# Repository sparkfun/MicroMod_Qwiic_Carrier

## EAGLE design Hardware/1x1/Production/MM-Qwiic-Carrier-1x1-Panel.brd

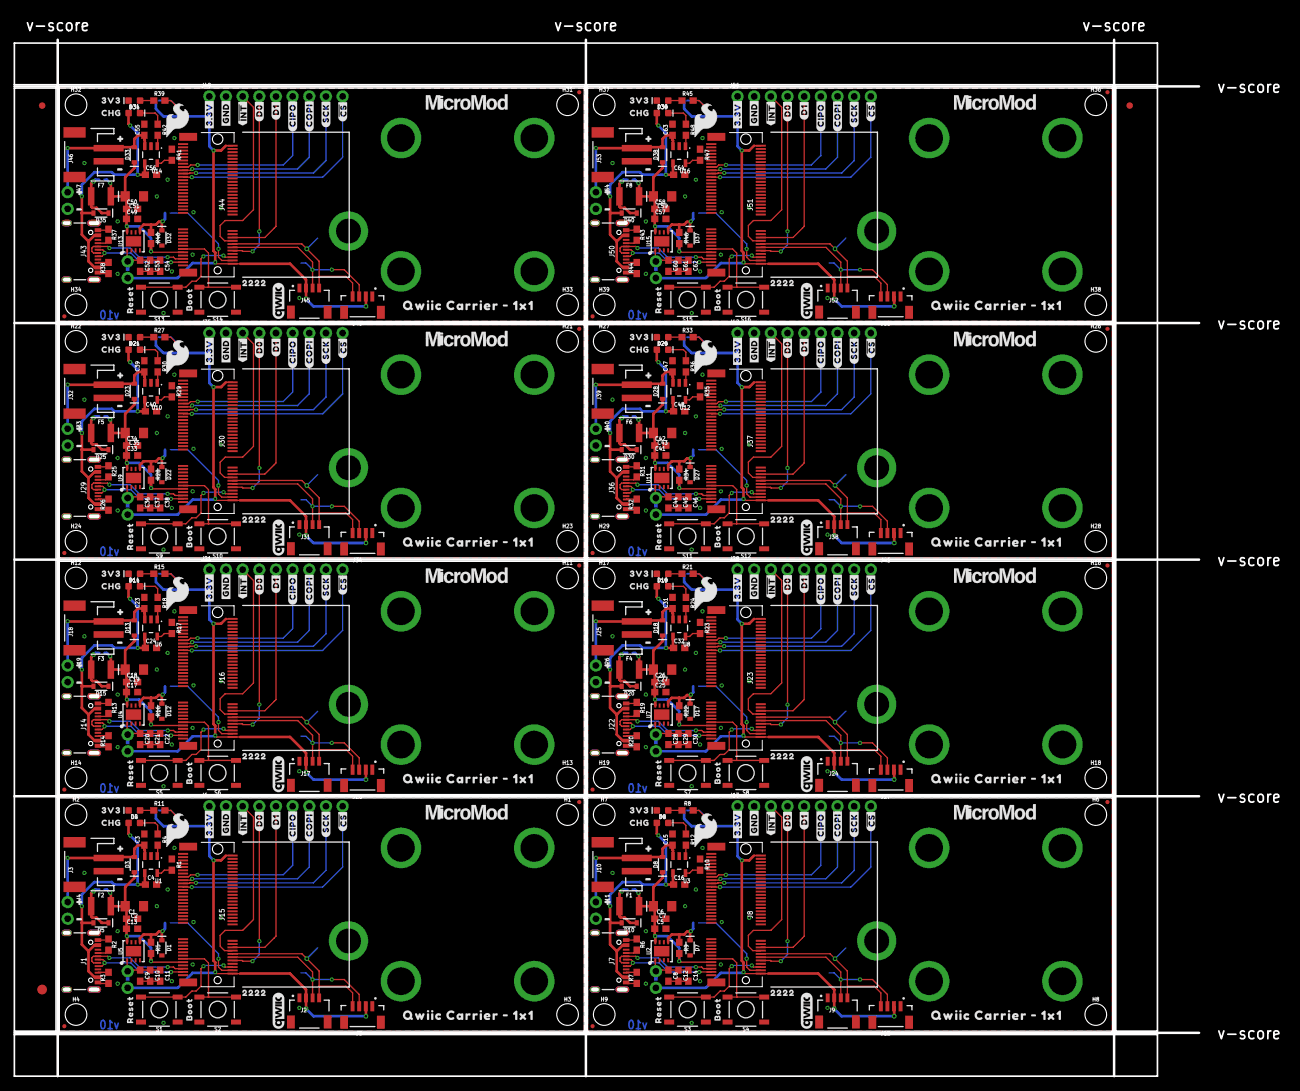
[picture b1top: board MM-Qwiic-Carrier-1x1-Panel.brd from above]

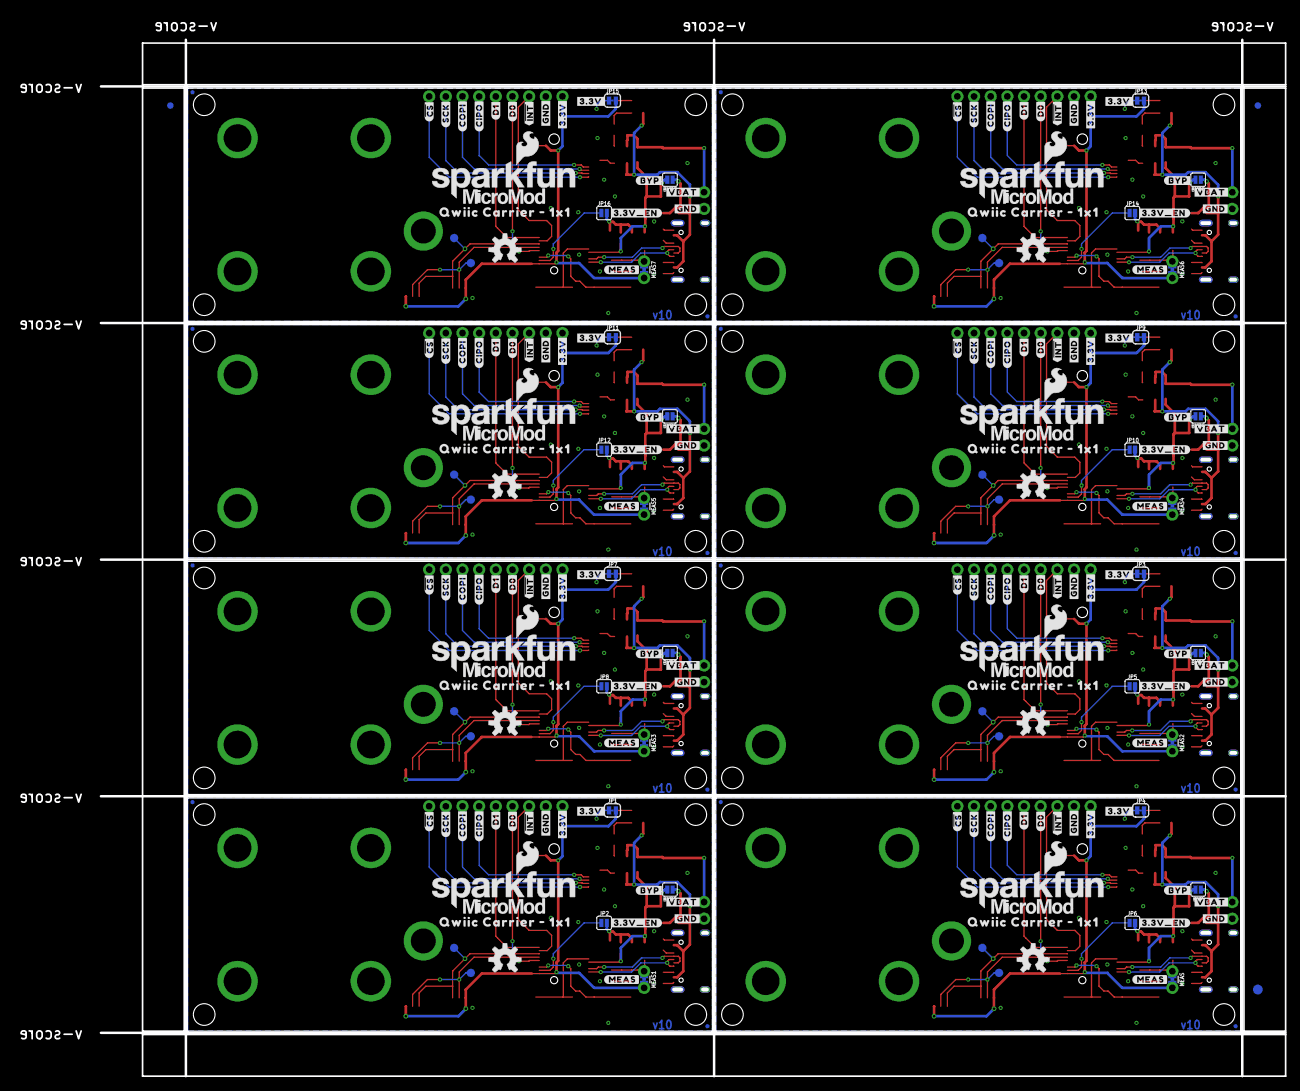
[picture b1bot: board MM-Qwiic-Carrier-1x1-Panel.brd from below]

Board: 2 copper layers, 180.6 x 158.0 mm, 710 parts (219 on the bottom side), 232 nets.

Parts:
BYP, BYP1, BYP2, BYP3, BYP4, BYP5, BYP6, BYP7: JUMPER-SMT_2_NO_SILK; SMT-JUMPER_2_NO_SILK
C1, C6, C18, C26, C34, C42, C50, C58: 0.1uF; 0603
C2, C7, C19, C27, C35, C43, C51, C59: 10uF; EIA3216
C3, C4, C15, C16, C23, C24, C31, C32, C39, C40, C47, C48, C55, C56, C63, C64: 4.7uF; 0603
C5, C11, C13, C14, C17, C22, C25, C30, C33, C38, C41, C46, C49, C54, C57, C62: 0.22uF; 0603
C8, C9, C20, C28, C36, C44, C52, C60: 10uF; 0603
C10, C12, C21, C29, C37, C45, C53, C61: 1.0uF; 0603
D1, D7, D12, D17, D22, D27, D32, D37: 3.3V; SOD-323
D2, D6, D11, D16, D21, D26, D31, D36: RED; LED-0603
D3, D5, D8, D10, D13, D15, D18, D20, D23, D25, D28, D30, D33, D35, D38, D40: 3A/10V/280mV; SOD-323
D4, D9, D14, D19, D24, D29, D34, D39: Yellow; LED-0603
E$1, E$2, E$3, E$4: FIDUCIAL-1X2
E$5, E$6: FIDUCIAL-1.5X3
F1, F2, F3, F4, F5, F6, F7, F8: 6V/2A; 1210
FD1, FD2, FD3, FD4, FD5, FD6, FD7, FD8, FD9, FD10, FD11, FD12, FD13, FD14, FD15, FD16, FD17, FD18, FD19, FD20, FD21, FD22, FD23, FD24, FD25, FD26, FD27, FD28, FD29, FD30, FD31, FD32: FIDUCIALUFIDUCIAL; FIDUCIAL-MICRO
H1, H2, H3, H4, H6, H7, H8, H9, H11, H12, H13, H14, H16, H17, H18, H19, H21, H22, H23, H24, H26, H27, H28, H29, H31, H32, H33, H34, H36, H37, H38, H39: STAND-OFF
H5, H10, H15, H20, H25, H30, H35, H40: STAND-OFF-REFLOW2.5MM_TALL; STAND-OFF-REFLOW-M2.5
J1, J7, J14, J22, J29, J36, J43, J50: USB-C-16P-2LAYER-PADS
J2, J9, J17, J24, J31, J38, J45, J52: QWIIC_RIGHT_ANGLE; JST04_1MM_RA
J3, J10, J18, J25, J32, J39, J46, J53: JST-2-SMD
J4, J11, J19, J26, J33, J40, J47, J54: 1X02_NO_SILK
J5, J12, J20, J27, J34, J41, J48, J55: Vertical Qwiic Connector; JST04_1MM_VERT
J6, J13, J21, J28, J35, J42, J49, J56: 1X09_NO_SILK
J8, J15, J16, J23, J30, J37, J44, J51: MICROMOD-2222-C; M.2-CONNECTOR-E
JP1, JP3, JP4, JP7, JP9, JP11, JP13, JP15: 3V3 LED; SMT-JUMPER_2_NC_TRACE_SILK
JP2, JP5, JP6, JP8, JP10, JP12, JP14, JP16: VE; SMT-JUMPER_2_NO_SILK
LOGO1, LOGO6, LOGO9, LOGO12, LOGO15, LOGO18, LOGO21, LOGO24: SFE_LOGO_NAME_FLAME.2_INCH; SFE_LOGO_NAME_FLAME_.2
LOGO2, LOGO4, LOGO7, LOGO10, LOGO13, LOGO16, LOGO19, LOGO22: QWIIC_LOGO_CONNECTOR; QWIIC_5.5MM
LOGO3, LOGO5, LOGO8, LOGO11, LOGO14, LOGO17, LOGO20, LOGO23: OSHW-LOGOM; OSHW-LOGO-M
MEAS, MEAS1, MEAS2, MEAS3, MEAS4, MEAS5, MEAS6, MEAS7: COMBO-JUMPER_2_NC_TRACE
R1, R10, R17, R23, R29, R35, R41, R47: 2.2k; 0603
R2, R3, R6, R7, R13, R14, R19, R20, R25, R26, R31, R32, R37, R38, R43, R44: 5.1k; 0603
R4, R8, R11, R12, R15, R18, R21, R24, R27, R30, R33, R36, R39, R42, R45, R48: 1k; 0603
R5, R9, R16, R22, R28, R34, R40, R46: 100k; 0603
S1, S3, S5, S7, S9, S11, S13, S15: Reset; TACTILE_SWITCH_SMD_5.2MM
S2, S4, S6, S8, S10, S12, S14, S16: BOOT; TACTILE_SWITCH_SMD_5.2MM
TP1, TP2, TP3, TP4, TP5, TP6, TP7, TP8, TP9, TP10, TP11, TP12, TP13, TP14, TP15, TP16: TEST-POINT3X5; PAD.03X.05
U1, U3, U6, U8, U10, U12, U14, U16: MCP73831; SOT23-5
U2, U4, U5, U7, U9, U11, U13, U15: AP7361C-33FGEUDFN-8; UDFN-8
U$1, U$49, U$90, U$129, U$168, U$207, U$246, U$285: #3#3V_EN#0
U$2, U$44, U$79, U$118, U$157, U$196, U$235, U$274: SFE_LOGO_FLAME_.2
U$3, U$48, U$89, U$128, U$167, U$206, U$245, U$284: 3V30
U$4, U$40, U$82, U$121, U$160, U$199, U$238, U$277: CHG0
U$5, U$45, U$86, U$125, U$164, U$203, U$242, U$281: QWIIC_BOARD_OUTLINESTANDOFF; QWIIC_BOARD_MOUNT_SMD_STANDOFFS
U$6, U$35, U$38, U$41, U$73, U$74, U$83, U$112, U$113, U$122, U$151, U$152, U$161, U$190, U$191, U$200, U$229, U$230, U$239, U$268, U$269, U$278, U$307, U$308: #3#3V#0
U$7, U$42, U$84, U$123, U$162, U$201, U$240, U$279: #BYP#0
U$8, U$14, U$33, U$50, U$51, U$59, U$91, U$92, U$100, U$130, U$131, U$139, U$169, U$170, U$178, U$208, U$209, U$217, U$247, U$248, U$256, U$286, U$287, U$295: #GND#0
U$9, U$43, U$85, U$124, U$163, U$202, U$241, U$280: #MEAS#0
U$10, U$13, U$46, U$47, U$87, U$88, U$126, U$127, U$165, U$166, U$204, U$205, U$243, U$244, U$282, U$283: QWIIC_CARRIER_#_1X10
U$11, U$32, U$36, U$37, U$60, U$61, U$62, U$63, U$101, U$102, U$103, U$104, U$140, U$141, U$142, U$143, U$179, U$180, U$181, U$182, U$218, U$219, U$220, U$221, U$257, U$258, U$259, U$260, U$296, U$297, U$298, U$299: #0
U$12, U$58, U$99, U$138, U$177, U$216, U$255, U$294: #VBAT#0
U$15, U$16, U$77, U$78, U$116, U$117, U$155, U$156, U$194, U$195, U$233, U$234, U$272, U$273, U$311, U$312: ##INT##0
U$17, U$18, U$64, U$65, U$105, U$106, U$144, U$145, U$183, U$184, U$222, U$223, U$261, U$262, U$300, U$301: #D0#0
U$19, U$39, U$67, U$68, U$80, U$81, U$119, U$120, U$158, U$159, U$197, U$198, U$236, U$237, U$275, U$276: MICROMOD_LOGO_.5
U$20, U$21, U$66, U$69, U$107, U$108, U$146, U$147, U$185, U$186, U$224, U$225, U$263, U$264, U$302, U$303: #D1#0
U$22, U$23, U$52, U$53, U$93, U$94, U$132, U$133, U$171, U$172, U$210, U$211, U$249, U$250, U$288, U$289: #CIPO#0
U$24, U$25, U$54, U$55, U$95, U$96, U$134, U$135, U$173, U$174, U$212, U$213, U$251, U$252, U$290, U$291: #COPI#0
U$26, U$27, U$56, U$57, U$97, U$98, U$136, U$137, U$175, U$176, U$214, U$215, U$253, U$254, U$292, U$293: #SCK#0
U$28, U$29, U$75, U$76, U$114, U$115, U$153, U$154, U$192, U$193, U$231, U$232, U$270, U$271, U$309, U$310: ##CS##0
U$30, U$70, U$109, U$148, U$187, U$226, U$265, U$304: RESET0
U$31, U$71, U$110, U$149, U$188, U$227, U$266, U$305: BOOT0
U$34, U$72, U$111, U$150, U$189, U$228, U$267, U$306: 22220

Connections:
3.3V: J2.2, J5.2, J6.1, J15.2, J15.74, JP4.2, MEAS.2, MEAS.4
3.3V1: J8.2, J8.74, J9.2, J12.2, J13.1, JP1.2, MEAS1.2, MEAS1.4
3.3V2: J16.2, J16.74, J17.2, J20.2, J21.1, JP3.2, MEAS2.2, MEAS2.4
3.3V3: J23.2, J23.74, J24.2, J27.2, J28.1, JP7.2, MEAS3.2, MEAS3.4
3.3V4: J30.2, J30.74, J31.2, J34.2, J35.1, JP9.2, MEAS4.2, MEAS4.4
3.3V5: J37.2, J37.74, J38.2, J41.2, J42.1, JP11.2, MEAS5.2, MEAS5.4
3.3V6: J44.2, J44.74, J45.2, J48.2, J49.1, JP13.2, MEAS6.2, MEAS6.4
3.3V7: J51.2, J51.74, J52.2, J55.2, J56.1, JP15.2, MEAS7.2, MEAS7.4
3.3V_EN: J15.4, JP6.1
3.3V_EN1: J8.4, JP2.1
3.3V_EN2: J16.4, JP5.1
3.3V_EN3: J23.4, JP8.1
3.3V_EN4: J30.4, JP10.1
3.3V_EN5: J37.4, JP12.1
3.3V_EN6: J44.4, JP14.1
3.3V_EN7: J51.4, JP16.1
!BOOT!: J15.11, S2.3, S2.4
!BOOT!1: J8.11, S4.3, S4.4
!BOOT!2: J16.11, S6.3, S6.4
!BOOT!3: J23.11, S8.3, S8.4
!BOOT!4: J30.11, S10.3, S10.4
!BOOT!5: J37.11, S12.3, S12.4
!BOOT!6: J44.11, S14.3, S14.4
!BOOT!7: J51.11, S16.3, S16.4
!RESET!: J15.6, S1.3, S1.4
!RESET!1: J8.6, S3.3, S3.4
!RESET!2: J16.6, S5.3, S5.4
!RESET!3: J23.6, S7.3, S7.4
!RESET!4: J30.6, S9.3, S9.4
!RESET!5: J37.6, S11.3, S11.4
!RESET!6: J44.6, S13.3, S13.4
!RESET!7: J51.6, S15.3, S15.4
D0: J6.4, J15.10
D1: J6.5, J15.18
D2: J8.10, J13.4
D3: J8.18, J13.5
D4: J16.10, J21.4
D5: J16.18, J21.5
D6: J23.10, J28.4
D7: J23.18, J28.5
D8: J30.10, J35.4
D9: J30.18, J35.5
D10: J37.10, J42.4
D11: J37.18, J42.5
D12: J44.10, J49.4
D13: J44.18, J49.5
D14: J51.10, J56.4
D15: J51.18, J56.5
GND: C1.2, C2.-, C3.2, C4.2, C9.2, C10.2, C11.2, C13.2, D1.A, D2.C, H5.1, J1.GND, J1.GND2, J2.1, J3.1, J4.2, J5.1, J6.2, J15.1, J15.7, J15.33, J15.36, J15.39, J15.45, J15.75, R1.1, R2.1, R3.1, S1.1, S1.2, S2.1, S2.2, U1.2, U5.4, U5.EP
GND1: C5.2, C6.2, C7.-, C8.2, C12.2, C14.2, C15.2, C16.2, D6.C, D7.A, H10.1, J7.GND, J7.GND2, J8.1, J8.7, J8.33, J8.36, J8.39, J8.45, J8.75, J9.1, J10.1, J11.2, J12.1, J13.2, R6.1, R7.1, R10.1, S3.1, S3.2, S4.1, S4.2, U2.4, U2.EP, U3.2
GND2: C17.2, C18.2, C19.-, C20.2, C21.2, C22.2, C23.2, C24.2, D11.C, D12.A, H15.1, J14.GND, J14.GND2, J16.1, J16.7, J16.33, J16.36, J16.39, J16.45, J16.75, J17.1, J18.1, J19.2, J20.1, J21.2, R13.1, R14.1, R17.1, S5.1, S5.2, S6.1, S6.2, U4.4, U4.EP, U6.2
GND3: C25.2, C26.2, C27.-, C28.2, C29.2, C30.2, C31.2, C32.2, D16.C, D17.A, H20.1, J22.GND, J22.GND2, J23.1, J23.7, J23.33, J23.36, J23.39, J23.45, J23.75, J24.1, J25.1, J26.2, J27.1, J28.2, R19.1, R20.1, R23.1, S7.1, S7.2, S8.1, S8.2, U7.4, U7.EP, U8.2
GND4: C33.2, C34.2, C35.-, C36.2, C37.2, C38.2, C39.2, C40.2, D21.C, D22.A, H25.1, J29.GND, J29.GND2, J30.1, J30.7, J30.33, J30.36, J30.39, J30.45, J30.75, J31.1, J32.1, J33.2, J34.1, J35.2, R25.1, R26.1, R29.1, S9.1, S9.2, S10.1, S10.2, U9.4, U9.EP, U10.2
GND5: C41.2, C42.2, C43.-, C44.2, C45.2, C46.2, C47.2, C48.2, D26.C, D27.A, H30.1, J36.GND, J36.GND2, J37.1, J37.7, J37.33, J37.36, J37.39, J37.45, J37.75, J38.1, J39.1, J40.2, J41.1, J42.2, R31.1, R32.1, R35.1, S11.1, S11.2, S12.1, S12.2, U11.4, U11.EP, U12.2
GND6: C49.2, C50.2, C51.-, C52.2, C53.2, C54.2, C55.2, C56.2, D31.C, D32.A, H35.1, J43.GND, J43.GND2, J44.1, J44.7, J44.33, J44.36, J44.39, J44.45, J44.75, J45.1, J46.1, J47.2, J48.1, J49.2, R37.1, R38.1, R41.1, S13.1, S13.2, S14.1, S14.2, U13.4, U13.EP, U14.2
GND7: C57.2, C58.2, C59.-, C60.2, C61.2, C62.2, C63.2, C64.2, D36.C, D37.A, H40.1, J50.GND, J50.GND2, J51.1, J51.7, J51.33, J51.36, J51.39, J51.45, J51.75, J52.1, J53.1, J54.2, J55.1, J56.2, R43.1, R44.1, R47.1, S15.1, S15.2, S16.1, S16.2, U15.4, U15.EP, U16.2
I2C_!INT!: J6.3, J15.16
I2C_!INT!1: J8.16, J13.3
I2C_!INT!2: J16.16, J21.3
I2C_!INT!3: J23.16, J28.3
I2C_!INT!4: J30.16, J35.3
I2C_!INT!5: J37.16, J42.3
I2C_!INT!6: J44.16, J49.3
I2C_!INT!7: J51.16, J56.3
unnamed: C9.1, C10.1, C11.1, MEAS.1, MEAS.3, U5.1
unnamed: R1.2, U1.5
unnamed: D4.C, R4.1
unnamed: JP4.1, R11.2
unnamed: J7.A5, R6.2
unnamed: D2.A, R11.1
unnamed: J7.B5, R7.2
unnamed: R4.2, U1.1
unnamed: JP1.1, R8.2
unnamed: J1.A5, R2.2
unnamed: J1.B5, R3.2
unnamed: D6.A, R8.1
unnamed: C8.1, C12.1, C14.1, MEAS1.1, MEAS1.3, U2.1
unnamed: R10.2, U3.5
unnamed: D9.C, R12.1
unnamed: R12.2, U3.1
unnamed: J14.A5, R13.2
unnamed: J14.B5, R14.2
unnamed: JP3.1, R15.2
unnamed: D11.A, R15.1
unnamed: C20.1, C21.1, C22.1, MEAS2.1, MEAS2.3, U4.1
unnamed: R17.2, U6.5
unnamed: D14.C, R18.1
unnamed: R18.2, U6.1
unnamed: J22.A5, R19.2
unnamed: J22.B5, R20.2
unnamed: JP7.1, R21.2
unnamed: D16.A, R21.1
unnamed: C28.1, C29.1, C30.1, MEAS3.1, MEAS3.3, U7.1
unnamed: R23.2, U8.5
unnamed: D19.C, R24.1
unnamed: R24.2, U8.1
unnamed: J29.A5, R25.2
unnamed: J29.B5, R26.2
unnamed: JP9.1, R27.2
unnamed: D21.A, R27.1
unnamed: C36.1, C37.1, C38.1, MEAS4.1, MEAS4.3, U9.1
unnamed: R29.2, U10.5
unnamed: D24.C, R30.1
unnamed: R30.2, U10.1
unnamed: J36.A5, R31.2
unnamed: J36.B5, R32.2
unnamed: JP11.1, R33.2
unnamed: D26.A, R33.1
unnamed: C44.1, C45.1, C46.1, MEAS5.1, MEAS5.3, U11.1
unnamed: R35.2, U12.5
unnamed: D29.C, R36.1
unnamed: R36.2, U12.1
unnamed: J43.A5, R37.2
unnamed: J43.B5, R38.2
unnamed: JP13.1, R39.2
unnamed: D31.A, R39.1
unnamed: C52.1, C53.1, C54.1, MEAS6.1, MEAS6.3, U13.1
unnamed: R41.2, U14.5
unnamed: D34.C, R42.1
unnamed: R42.2, U14.1
unnamed: J50.A5, R43.2
unnamed: J50.B5, R44.2
unnamed: JP15.1, R45.2
unnamed: D36.A, R45.1
unnamed: C60.1, C61.1, C62.1, MEAS7.1, MEAS7.3, U15.1
unnamed: R47.2, U16.5
unnamed: D39.C, R48.1
unnamed: R48.2, U16.1
SCL: J2.4, J5.4, J15.14, TP2.P$1
SCL1: J8.14, J9.4, J12.4, TP4.P$1
SCL2: J16.14, J17.4, J20.4, TP6.P$1
SCL3: J23.14, J24.4, J27.4, TP8.P$1
SCL4: J30.14, J31.4, J34.4, TP10.P$1
SCL5: J37.14, J38.4, J41.4, TP12.P$1
SCL6: J44.14, J45.4, J48.4, TP14.P$1
SCL7: J51.14, J52.4, J55.4, TP16.P$1
SDA: J2.3, J5.3, J15.12, TP1.P$1
SDA1: J8.12, J9.3, J12.3, TP3.P$1
SDA2: J16.12, J17.3, J20.3, TP5.P$1
SDA3: J23.12, J24.3, J27.3, TP7.P$1
SDA4: J30.12, J31.3, J34.3, TP9.P$1
SDA5: J37.12, J38.3, J41.3, TP11.P$1
SDA6: J44.12, J45.3, J48.3, TP13.P$1
SDA7: J51.12, J52.3, J55.3, TP15.P$1
SPI_!CS!: J6.9, J15.55
SPI_!CS!1: J8.55, J13.9
SPI_!CS!2: J16.55, J21.9
SPI_!CS!3: J23.55, J28.9
SPI_!CS!4: J30.55, J35.9
SPI_!CS!5: J37.55, J42.9
SPI_!CS!6: J44.55, J49.9
SPI_!CS!7: J51.55, J56.9
SPI_CIPO: J6.6, J15.61
SPI_CIPO1: J8.61, J13.6
SPI_CIPO2: J16.61, J21.6
SPI_CIPO3: J23.61, J28.6
SPI_CIPO4: J30.61, J35.6
SPI_CIPO5: J37.61, J42.6
SPI_CIPO6: J44.61, J49.6
SPI_CIPO7: J51.61, J56.6
SPI_COPI: J6.7, J15.59
SPI_COPI1: J8.59, J13.7
SPI_COPI2: J16.59, J21.7
SPI_COPI3: J23.59, J28.7
SPI_COPI4: J30.59, J35.7
SPI_COPI5: J37.59, J42.7
SPI_COPI6: J44.59, J49.7
SPI_COPI7: J51.59, J56.7
SPI_SCK: J6.8, J15.57
SPI_SCK1: J8.57, J13.8
SPI_SCK2: J16.57, J21.8
SPI_SCK3: J23.57, J28.8
SPI_SCK4: J30.57, J35.8
SPI_SCK5: J37.57, J42.8
SPI_SCK6: J44.57, J49.8
SPI_SCK7: J51.57, J56.8
USB_D+: J1.A6, J1.B6, J15.3
USB_D+1: J7.A6, J7.B6, J8.3
USB_D+2: J14.A6, J14.B6, J16.3
USB_D+3: J22.A6, J22.B6, J23.3
USB_D+4: J29.A6, J29.B6, J30.3
USB_D+5: J36.A6, J36.B6, J37.3
USB_D+6: J43.A6, J43.B6, J44.3
USB_D+7: J50.A6, J50.B6, J51.3
USB_D-: J1.A7, J1.B7, J15.5
USB_D-1: J7.A7, J7.B7, J8.5
USB_D-2: J14.A7, J14.B7, J16.5
USB_D-3: J22.A7, J22.B7, J23.5
USB_D-4: J29.A7, J29.B7, J30.5
USB_D-5: J36.A7, J36.B7, J37.5
USB_D-6: J43.A7, J43.B7, J44.5
USB_D-7: J50.A7, J50.B7, J51.5
VIN: BYP.2, C1.1, C2.+, C13.1, D3.C, F2.2, J15.9, R5.2, U5.8
VIN1: BYP1.2, C5.1, C6.1, C7.+, D8.C, F1.2, J8.9, R9.2, U2.8
VIN2: BYP2.2, C17.1, C18.1, C19.+, D13.C, F3.2, J16.9, R16.2, U4.8
VIN3: BYP3.2, C25.1, C26.1, C27.+, D18.C, F4.2, J23.9, R22.2, U7.8
VIN4: BYP4.2, C33.1, C34.1, C35.+, D23.C, F5.2, J30.9, R28.2, U9.8
VIN5: BYP5.2, C41.1, C42.1, C43.+, D28.C, F6.2, J37.9, R34.2, U11.8
VIN6: BYP6.2, C49.1, C50.1, C51.+, D33.C, F7.2, J44.9, R40.2, U13.8
VIN7: BYP7.2, C57.1, C58.1, C59.+, D38.C, F8.2, J51.9, R46.2, U15.8
VREG_EN: D1.C, JP6.2, R5.1, U5.5
VREG_EN1: D7.C, JP2.2, R9.1, U2.5
VREG_EN2: D12.C, JP5.2, R16.1, U4.5
VREG_EN3: D17.C, JP8.2, R22.1, U7.5
VREG_EN4: D22.C, JP10.2, R28.1, U9.5
VREG_EN5: D27.C, JP12.2, R34.1, U11.5
VREG_EN6: D32.C, JP14.2, R40.1, U13.5
VREG_EN7: D37.C, JP16.2, R46.1, U15.5
V_BATT: C3.1, D3.A, J3.2, J4.1, U1.3
V_BATT1: C15.1, D8.A, J10.2, J11.1, U3.3
V_BATT2: C23.1, D13.A, J18.2, J19.1, U6.3
V_BATT3: C31.1, D18.A, J25.2, J26.1, U8.3
V_BATT4: C39.1, D23.A, J32.2, J33.1, U10.3
V_BATT5: C47.1, D28.A, J39.2, J40.1, U12.3
V_BATT6: C55.1, D33.A, J46.2, J47.1, U14.3
V_BATT7: C63.1, D38.A, J53.2, J54.1, U16.3
V_USB: C4.1, D4.A, D5.A, J1.VBUS1, J1.VBUS2, U1.4
V_USB1: C16.1, D9.A, D10.A, J7.VBUS1, J7.VBUS2, U3.4
V_USB2: C24.1, D14.A, D15.A, J14.VBUS1, J14.VBUS2, U6.4
V_USB3: C32.1, D19.A, D20.A, J22.VBUS1, J22.VBUS2, U8.4
V_USB4: C40.1, D24.A, D25.A, J29.VBUS1, J29.VBUS2, U10.4
V_USB5: C48.1, D29.A, D30.A, J36.VBUS1, J36.VBUS2, U12.4
V_USB6: C56.1, D34.A, D35.A, J43.VBUS1, J43.VBUS2, U14.4
V_USB7: C64.1, D39.A, D40.A, J50.VBUS1, J50.VBUS2, U16.4
V_USB_1: BYP1.1, D10.C, F1.1
V_USB_2: BYP.1, D5.C, F2.1
V_USB_3: BYP2.1, D15.C, F3.1
V_USB_4: BYP3.1, D20.C, F4.1
V_USB_5: BYP4.1, D25.C, F5.1
V_USB_6: BYP5.1, D30.C, F6.1
V_USB_7: BYP6.1, D35.C, F7.1
V_USB_8: BYP7.1, D40.C, F8.1

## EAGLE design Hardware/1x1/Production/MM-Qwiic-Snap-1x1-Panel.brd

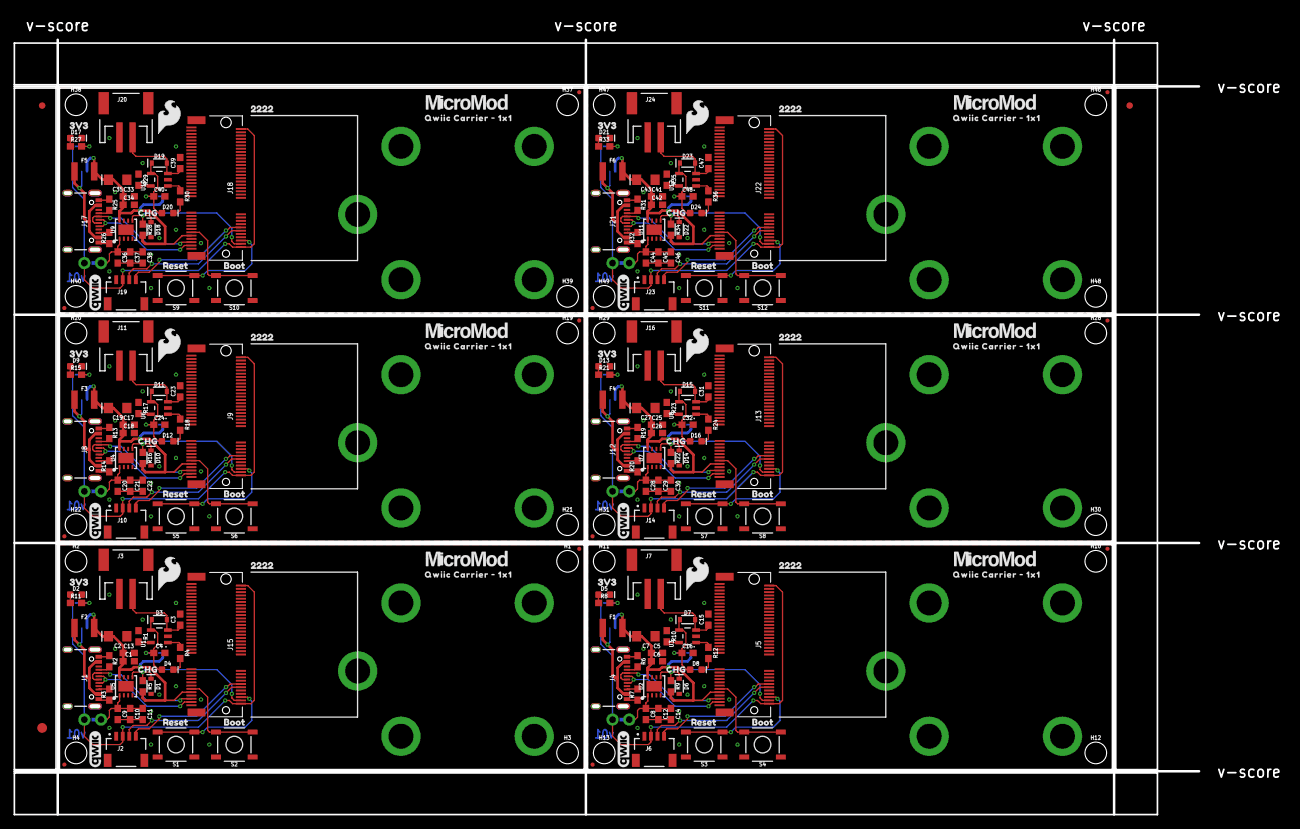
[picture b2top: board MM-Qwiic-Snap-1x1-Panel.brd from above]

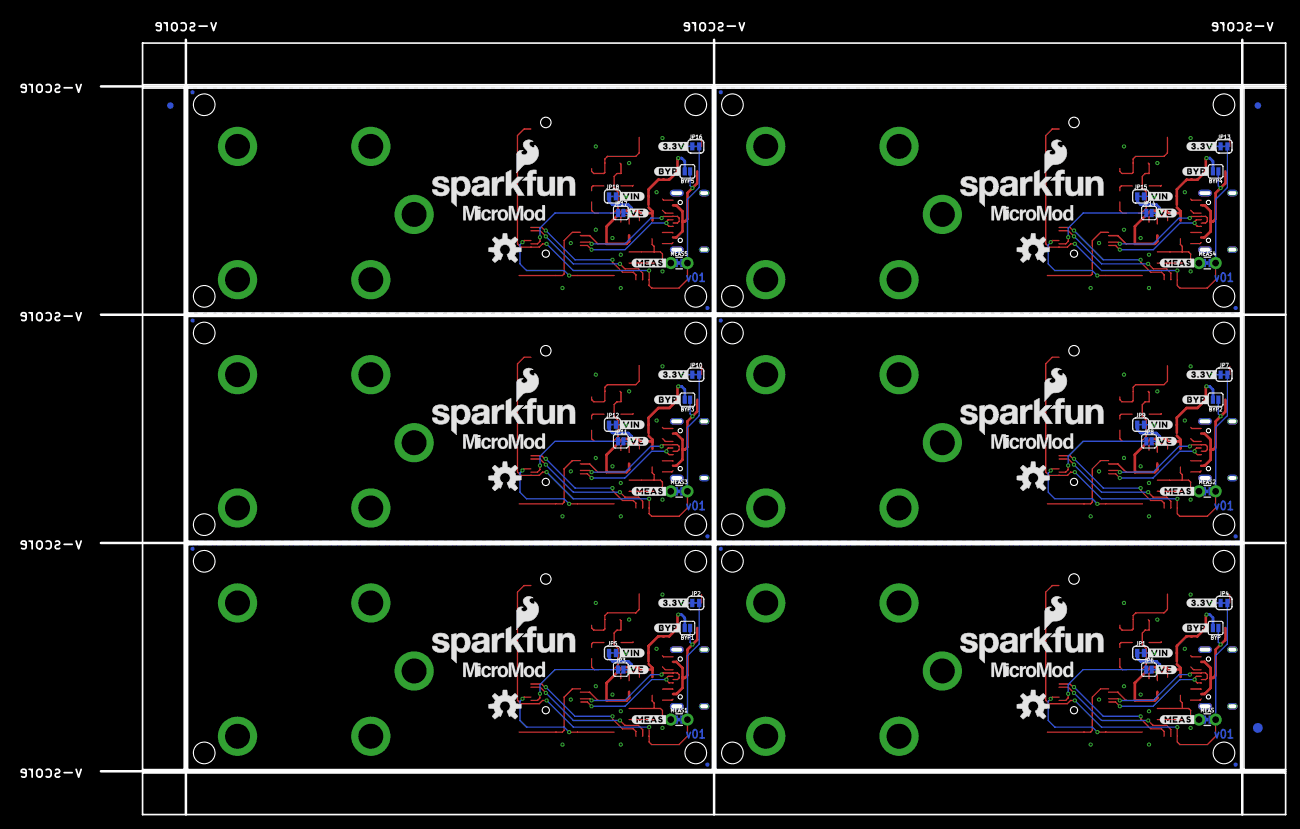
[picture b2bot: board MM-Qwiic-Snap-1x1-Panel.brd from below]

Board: 2 copper layers, 180.6 x 118.1 mm, 378 parts (93 on the bottom side), 132 nets.

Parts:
BYP, BYP1, BYP2, BYP3, BYP4, BYP5: JUMPER-SMT_2_NO_SILK; SMT-JUMPER_2_NO_SILK
C1, C6, C18, C26, C34, C42: 0.1uF; 0603
C2, C7, C19, C27, C35, C43: 10uF; EIA3216
C3, C4, C15, C16, C23, C24, C31, C32, C39, C40, C47, C48: 4.7uF; 0603
C5, C11, C13, C14, C17, C22, C25, C30, C33, C38, C41, C46: 0.22uF; 0603
C8, C9, C20, C28, C36, C44: 10uF; 0603
C10, C12, C21, C29, C37, C45: 1.0uF; 0603
D1, D6, D10, D14, D18, D22: 3.3V; SOD-323
D2, D5, D9, D13, D17, D21: RED; LED-0603
D3, D7, D11, D15, D19, D23: 3A/10V/280mV; SOD-323
D4, D8, D12, D16, D20, D24: Yellow; LED-0603
E$1, E$2, E$3, E$4: FIDUCIAL-1X2
E$5, E$6: FIDUCIAL-1.5X3
F1, F2, F3, F4, F5, F6: 6V/2A; 1210
FD1, FD2, FD3, FD4, FD5, FD6, FD7, FD8, FD9, FD10, FD11, FD12, FD13, FD14, FD15, FD16, FD17, FD18, FD19, FD20, FD21, FD22, FD23, FD24: FIDUCIALUFIDUCIAL; FIDUCIAL-MICRO
H1, H2, H3, H4, H10, H11, H12, H13, H19, H20, H21, H22, H28, H29, H30, H31, H37, H38, H39, H40, H46, H47, H48, H49: STAND-OFF
H5, H6, H7, H8, H9, H14, H15, H16, H17, H18, H23, H24, H25, H26, H27, H32, H33, H34, H35, H36, H41, H42, H43, H44, H45, H50, H51, H52, H53, H54: STAND-OFF-REFLOW2.5MM_TALL; STAND-OFF-REFLOW-M2.5
J1, J4, J8, J12, J17, J21: USB-C-16P-2LAYER-PADS
J2, J6, J10, J14, J19, J23: QWIIC_RIGHT_ANGLE; JST04_1MM_RA
J3, J7, J11, J16, J20, J24: JST-2-SMD
J5, J9, J13, J15, J18, J22: MICROMOD-2222-C; M.2-CONNECTOR-E
JP1, JP5, JP9, JP12, JP15, JP18: JUMPER-SMT_2_NC_TRACE_SILK; SMT-JUMPER_2_NC_TRACE_SILK
JP2, JP4, JP7, JP10, JP13, JP16: 3V3 LED; SMT-JUMPER_2_NC_TRACE_SILK
JP3, JP6, JP8, JP11, JP14, JP17: VE; SMT-JUMPER_2_NO_SILK
LOGO1, LOGO6, LOGO9, LOGO12, LOGO15, LOGO18: SFE_LOGO_NAME_FLAME.2_INCH; SFE_LOGO_NAME_FLAME_.2
LOGO2, LOGO4, LOGO7, LOGO10, LOGO13, LOGO16: QWIIC_LOGO_CONNECTOR; QWIIC_5.5MM
LOGO3, LOGO5, LOGO8, LOGO11, LOGO14, LOGO17: OSHW-LOGOM; OSHW-LOGO-M
MEAS, MEAS1, MEAS2, MEAS3, MEAS4, MEAS5: COMBO-JUMPER_2_NC_TRACE
R1, R10, R17, R23, R29, R35: 2.2k; 0603
R2, R3, R6, R7, R13, R14, R19, R20, R25, R26, R31, R32: 5.1k; 0603
R4, R8, R11, R12, R15, R18, R21, R24, R27, R30, R33, R36: 1k; 0603
R5, R9, R16, R22, R28, R34: 100k; 0603
S1, S3, S5, S7, S9, S11: Reset; TACTILE_SWITCH_SMD_5.2MM
S2, S4, S6, S8, S10, S12: BOOT; TACTILE_SWITCH_SMD_5.2MM
U1, U3, U6, U8, U10, U12: MCP73831; SOT23-5
U2, U4, U5, U7, U9, U11: AP7361C-33FGEUDFN-8; UDFN-8
U$1, U$13, U$28, U$42, U$58, U$74: 3V31
U$2, U$10, U$25, U$39, U$54, U$71: RESET3
U$3, U$17, U$32, U$47, U$62, U$78: QWIIC_CARRIER_#_1X1_0
U$4, U$18, U$33, U$48, U$63, U$79: CHG0
U$5, U$23, U$37, U$52, U$69, U$83: #VIN#0
U$6, U$20, U$34, U$49, U$64, U$80: #3#3V#0
U$7, U$21, U$35, U$50, U$65, U$81: #BYP#0
U$8, U$24, U$38, U$53, U$70, U$84: #VE#0
U$9, U$22, U$36, U$51, U$66, U$82: #MEAS#0
U$11, U$19, U$26, U$40, U$56, U$72: BOOT2
U$12, U$27, U$41, U$55, U$57, U$73: 22229
U$14, U$29, U$43, U$44, U$59, U$75: SFE_LOGO_FLAME_.2
U$15, U$16, U$30, U$31, U$45, U$46, U$60, U$61, U$67, U$68, U$76, U$77: MICROMOD_LOGO_.5

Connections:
3.3V: J2.2, J15.2, J15.74, JP4.2, MEAS.2, MEAS.4
3.3V1: J5.2, J5.74, J6.2, JP2.2, MEAS1.2, MEAS1.4
3.3V2: J9.2, J9.74, J10.2, JP7.2, MEAS2.2, MEAS2.4
3.3V3: J13.2, J13.74, J14.2, JP10.2, MEAS3.2, MEAS3.4
3.3V4: J18.2, J18.74, J19.2, JP13.2, MEAS4.2, MEAS4.4
3.3V5: J22.2, J22.74, J23.2, JP16.2, MEAS5.2, MEAS5.4
3.3V_EN: J15.4, JP6.1
3.3V_EN1: J5.4, JP3.1
3.3V_EN2: J9.4, JP8.1
3.3V_EN3: J13.4, JP11.1
3.3V_EN4: J18.4, JP14.1
3.3V_EN5: J22.4, JP17.1
5V: C4.1, D3.C, D4.A, JP1.2, U1.4
5V1: C16.1, D7.C, D8.A, JP5.2, U3.4
5V2: C24.1, D11.C, D12.A, JP9.2, U6.4
5V3: C32.1, D15.C, D16.A, JP12.2, U8.4
5V4: C40.1, D19.C, D20.A, JP15.2, U10.4
5V5: C48.1, D23.C, D24.A, JP18.2, U12.4
!BOOT!: J15.11, S2.3, S2.4
!BOOT!1: J5.11, S4.3, S4.4
!BOOT!2: J9.11, S6.3, S6.4
!BOOT!3: J13.11, S8.3, S8.4
!BOOT!4: J18.11, S10.3, S10.4
!BOOT!5: J22.11, S12.3, S12.4
!RESET!: J15.6, S1.3, S1.4
!RESET!1: J5.6, S3.3, S3.4
!RESET!2: J9.6, S5.3, S5.4
!RESET!3: J13.6, S7.3, S7.4
!RESET!4: J18.6, S9.3, S9.4
!RESET!5: J22.6, S11.3, S11.4
GND: C1.2, C2.-, C3.2, C4.2, C9.2, C10.2, C11.2, C13.2, D1.A, D2.C, H5.1, H6.1, H7.1, H8.1, H9.1, J1.GND, J1.GND2, J2.1, J3.1, J15.1, J15.7, J15.33, J15.36, J15.39, J15.45, J15.75, R1.1, R2.1, R3.1, S1.1, S1.2, S2.1, S2.2, U1.2, U5.4, U5.EP
GND1: C5.2, C6.2, C7.-, C8.2, C12.2, C14.2, C15.2, C16.2, D5.C, D6.A, H14.1, H15.1, H16.1, H17.1, H18.1, J4.GND, J4.GND2, J5.1, J5.7, J5.33, J5.36, J5.39, J5.45, J5.75, J6.1, J7.1, R6.1, R7.1, R10.1, S3.1, S3.2, S4.1, S4.2, U2.4, U2.EP, U3.2
GND2: C17.2, C18.2, C19.-, C20.2, C21.2, C22.2, C23.2, C24.2, D9.C, D10.A, H23.1, H24.1, H25.1, H26.1, H27.1, J8.GND, J8.GND2, J9.1, J9.7, J9.33, J9.36, J9.39, J9.45, J9.75, J10.1, J11.1, R13.1, R14.1, R17.1, S5.1, S5.2, S6.1, S6.2, U4.4, U4.EP, U6.2
GND3: C25.2, C26.2, C27.-, C28.2, C29.2, C30.2, C31.2, C32.2, D13.C, D14.A, H32.1, H33.1, H34.1, H35.1, H36.1, J12.GND, J12.GND2, J13.1, J13.7, J13.33, J13.36, J13.39, J13.45, J13.75, J14.1, J16.1, R19.1, R20.1, R23.1, S7.1, S7.2, S8.1, S8.2, U7.4, U7.EP, U8.2
GND4: C33.2, C34.2, C35.-, C36.2, C37.2, C38.2, C39.2, C40.2, D17.C, D18.A, H41.1, H42.1, H43.1, H44.1, H45.1, J17.GND, J17.GND2, J18.1, J18.7, J18.33, J18.36, J18.39, J18.45, J18.75, J19.1, J20.1, R25.1, R26.1, R29.1, S9.1, S9.2, S10.1, S10.2, U9.4, U9.EP, U10.2
GND5: C41.2, C42.2, C43.-, C44.2, C45.2, C46.2, C47.2, C48.2, D21.C, D22.A, H50.1, H51.1, H52.1, H53.1, H54.1, J21.GND, J21.GND2, J22.1, J22.7, J22.33, J22.36, J22.39, J22.45, J22.75, J23.1, J24.1, R31.1, R32.1, R35.1, S11.1, S11.2, S12.1, S12.2, U11.4, U11.EP, U12.2
I2C_SCL: J2.4, J15.14
I2C_SCL1: J5.14, J6.4
I2C_SCL2: J9.14, J10.4
I2C_SCL3: J13.14, J14.4
I2C_SCL4: J18.14, J19.4
I2C_SCL5: J22.14, J23.4
I2C_SDA: J2.3, J15.12
I2C_SDA1: J5.12, J6.3
I2C_SDA2: J9.12, J10.3
I2C_SDA3: J13.12, J14.3
I2C_SDA4: J18.12, J19.3
I2C_SDA5: J22.12, J23.3
unnamed: C9.1, C10.1, C11.1, MEAS.1, MEAS.3, U5.1
unnamed: R1.2, U1.5
unnamed: R4.1, U1.1
unnamed: JP4.1, R11.2
unnamed: C3.1, D3.A, J3.2, U1.3
unnamed: D2.A, R11.1
unnamed: J4.A5, R6.2
unnamed: D4.C, R4.2
unnamed: J4.B5, R7.2
unnamed: J1.A5, R2.2
unnamed: J1.B5, R3.2
unnamed: JP2.1, R8.2
unnamed: D5.A, R8.1
unnamed: C8.1, C12.1, C14.1, MEAS1.1, MEAS1.3, U2.1
unnamed: R10.2, U3.5
unnamed: C15.1, D7.A, J7.2, U3.3
unnamed: R12.1, U3.1
unnamed: D8.C, R12.2
unnamed: J8.A5, R13.2
unnamed: J8.B5, R14.2
unnamed: JP7.1, R15.2
unnamed: D9.A, R15.1
unnamed: C20.1, C21.1, C22.1, MEAS2.1, MEAS2.3, U4.1
unnamed: R17.2, U6.5
unnamed: C23.1, D11.A, J11.2, U6.3
unnamed: R18.1, U6.1
unnamed: D12.C, R18.2
unnamed: J12.A5, R19.2
unnamed: J12.B5, R20.2
unnamed: JP10.1, R21.2
unnamed: D13.A, R21.1
unnamed: C28.1, C29.1, C30.1, MEAS3.1, MEAS3.3, U7.1
unnamed: R23.2, U8.5
unnamed: C31.1, D15.A, J16.2, U8.3
unnamed: R24.1, U8.1
unnamed: D16.C, R24.2
unnamed: J17.A5, R25.2
unnamed: J17.B5, R26.2
unnamed: JP13.1, R27.2
unnamed: D17.A, R27.1
unnamed: C36.1, C37.1, C38.1, MEAS4.1, MEAS4.3, U9.1
unnamed: R29.2, U10.5
unnamed: C39.1, D19.A, J20.2, U10.3
unnamed: R30.1, U10.1
unnamed: D20.C, R30.2
unnamed: J21.A5, R31.2
unnamed: J21.B5, R32.2
unnamed: JP16.1, R33.2
unnamed: D21.A, R33.1
unnamed: C44.1, C45.1, C46.1, MEAS5.1, MEAS5.3, U11.1
unnamed: R35.2, U12.5
unnamed: C47.1, D23.A, J24.2, U12.3
unnamed: R36.1, U12.1
unnamed: D24.C, R36.2
USB_D+: J1.A6, J1.B6, J15.3
USB_D+1: J4.A6, J4.B6, J5.3
USB_D+2: J8.A6, J8.B6, J9.3
USB_D+3: J12.A6, J12.B6, J13.3
USB_D+4: J17.A6, J17.B6, J18.3
USB_D+5: J21.A6, J21.B6, J22.3
USB_D-: J1.A7, J1.B7, J15.5
USB_D-1: J4.A7, J4.B7, J5.5
USB_D-2: J8.A7, J8.B7, J9.5
USB_D-3: J12.A7, J12.B7, J13.5
USB_D-4: J17.A7, J17.B7, J18.5
USB_D-5: J21.A7, J21.B7, J22.5
VIN: BYP.2, C1.1, C2.+, C13.1, F2.2, J15.9, JP1.1, R5.2, U5.8
VIN1: BYP1.2, C5.1, C6.1, C7.+, F1.2, J5.9, JP5.1, R9.2, U2.8
VIN2: BYP2.2, C17.1, C18.1, C19.+, F3.2, J9.9, JP9.1, R16.2, U4.8
VIN3: BYP3.2, C25.1, C26.1, C27.+, F4.2, J13.9, JP12.1, R22.2, U7.8
VIN4: BYP4.2, C33.1, C34.1, C35.+, F5.2, J18.9, JP15.1, R28.2, U9.8
VIN5: BYP5.2, C41.1, C42.1, C43.+, F6.2, J22.9, JP18.1, R34.2, U11.8
VREG_EN: D1.C, JP6.2, R5.1, U5.5
VREG_EN1: D6.C, JP3.2, R9.1, U2.5
VREG_EN2: D10.C, JP8.2, R16.1, U4.5
VREG_EN3: D14.C, JP11.2, R22.1, U7.5
VREG_EN4: D18.C, JP14.2, R28.1, U9.5
VREG_EN5: D22.C, JP17.2, R34.1, U11.5
V_USB: BYP.1, F2.1, J1.VBUS1, J1.VBUS2
V_USB1: BYP1.1, F1.1, J4.VBUS1, J4.VBUS2
V_USB2: BYP2.1, F3.1, J8.VBUS1, J8.VBUS2
V_USB3: BYP3.1, F4.1, J12.VBUS1, J12.VBUS2
V_USB4: BYP4.1, F5.1, J17.VBUS1, J17.VBUS2
V_USB5: BYP5.1, F6.1, J21.VBUS1, J21.VBUS2

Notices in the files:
parts and their libraries:
SparkFun-Aesthetics: Licensing: Creative Commons ShareAlike 4.0 International - https://creativecommons.org/licenses/by-sa/4.0
